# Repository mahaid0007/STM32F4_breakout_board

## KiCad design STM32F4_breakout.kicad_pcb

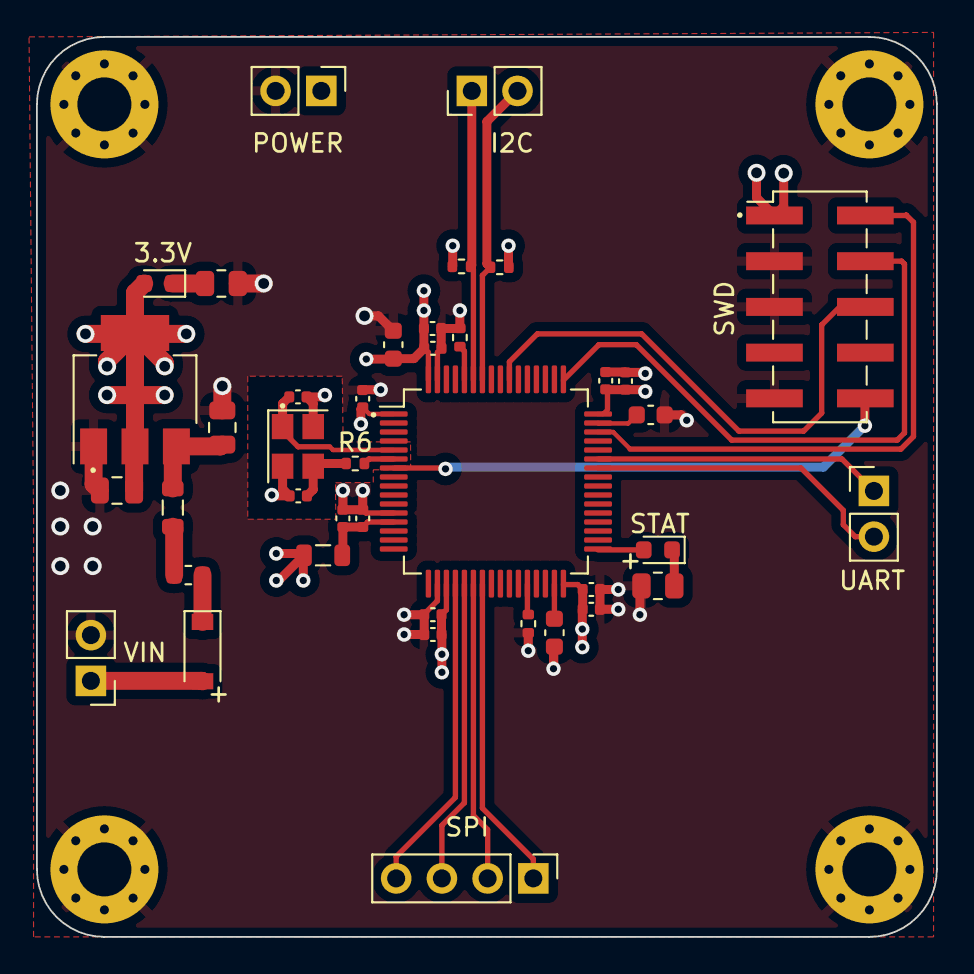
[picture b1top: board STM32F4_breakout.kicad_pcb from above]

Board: 4 copper layers, 50.0 x 50.0 mm, 44 parts (0 on the bottom side), 29 nets.

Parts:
3.3V: LED; LED_0603_1608Metric
3.3V#2: 3.3v; PinHeader_1x02_P2.54mm_Vertical
C1, C2: 10u; C_0805_2012Metric
C3: 10u; C_0603_1608Metric
C4, C5, C6, C7, C8, C9, C10, C11, C12, C13: 100n; C_0402_1005Metric
C14: 10n; C_0402_1005Metric
C15, C16: 2.2u; C_0603_1608Metric
C17, C18: 12p; C_0402_1005Metric
F1: 500mA; Fuse_0603_1608Metric
FB1, FB2: 100R; L_0805_2012Metric
Fuse: B5819W; D_SOD-123
H1, H2, H3, H4: MountingHole_Pad; MountingHole_3mm_Pad_Via
I2C: I2C; PinHeader_1x02_P2.54mm_Vertical
J1: VCC; PinHeader_1x02_P2.54mm_Vertical
R1, R7: 2K2; R_0805_2012Metric
R2, R3: 10k; R_0402_1005Metric
R4, R5: 2K2; R_0402_1005Metric
R6: 220; R_0402_1005Metric
SPI: SPI; PinHeader_1x04_P2.54mm_Vertical
STAT: LED; LED_0603_1608Metric
SWD: Conn_02x05_Odd_Even; PinHeader_2x05_P2.54mm_Vertical_SMD
U1: AMS1117-3.3; SOT-223-3_TabPin2
U2: STM32F405RGTx; LQFP-64_10x10mm_P0.5mm
UART: UART; PinHeader_1x02_P2.54mm_Vertical
XTAL: 16MHz; Crystal_SMD_3225-4Pin_3.2x2.5mm

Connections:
+3.3VA: C13.1, C14.1, FB2.2, U2.13 (VDDA)
+3V3: 3.3V.2 (A), 3.3V#2.1, C2.1, C3.1, C4.1, C5.1, C6.1, C7.1, C8.1, C9.1, C10.1, C11.1, C12.1, FB2.1, R4.1, R5.1, SWD.1, U1.2 (VO), U2.1 (VBAT), U2.19 (VDD), U2.32 (VDD), U2.48 (VDD), U2.64 (VDD)
BOOT0: R2.2, U2.60 (BOOT0)
BOOT1: R3.2, U2.28 (PB2)
GND: 3.3V#2.2, C1.2, C2.2, C3.2, C4.2, C5.2, C6.2, C7.2, C8.2, C9.2, C10.2, C11.2, C12.2, C13.2, C14.2, C15.2, C16.2, C17.2, C18.2, H1.1, H2.1, H3.1, H4.1, J1.2, R1.2, R2.1, R3.1, R7.2, SWD.3, SWD.5, SWD.9, U1.1 (GND), U2.12 (VSSA), U2.18 (VSS), U2.63 (VSS), XTAL.2, XTAL.4
HSE_IN: C17.1, U2.5 (PH0), XTAL.1
HSE_OUT: R6.2, U2.6 (PH1)
I2C1_SCL: I2C.2, R4.2, U2.58 (PB6)
I2C1_SDA: I2C.1, R5.2, U2.59 (PB7)
NRST: SWD.10, U2.7 (NRST)
unnamed: C1.1, FB1.1, U1.3 (VI)
unnamed: C15.1, U2.31 (VCAP_1)
unnamed: C16.1, U2.47 (VCAP_2)
unnamed: C18.1, R6.1, XTAL.3
unnamed: F1.1, Fuse.1 (K)
unnamed: 3.3V.1 (K), R1.1
unnamed: R7.1, STAT.1 (K)
unnamed: STAT.2 (A), U2.33 (PB12)
unnamed: F1.2, FB1.2
SPI1_CS: SPI.4, U2.20 (PA4)
SPI1_MISO: SPI.2, U2.22 (PA6)
SPI1_MOSI: SPI.1, U2.23 (PA7)
SPI1_SCK: SPI.3, U2.21 (PA5)
SWCLK: SWD.4, U2.49 (PA14)
SWDIO: SWD.2, U2.46 (PA13)
SWO: SWD.6, U2.55 (PB3)
UART1_RX: U2.43 (PA10), UART.1
UART1_TX: U2.42 (PA9), UART.2
VCC: Fuse.2 (A), J1.1

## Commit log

2023-03-22 smt32f4 breakout board
2023-03-22 third commit
